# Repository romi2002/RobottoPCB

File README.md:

## Robotto PCB
PCB board designed to control a small, four wheeled robot, using a Teensy 4.0 as the main controller.

## Features
- Uses a `Teensy 4.0` or a `Teensy 4.1` (without soldering in the extra headers)
- 4 VNH5019A drivers
- Support for 5V or 3.3V encoders
- Raspberry PI GPIO compatible header
- Current and voltage monitoring
- Support for adding an IMU

## Warning!
This board has several known issues, further revisions to the PCB design have to be made.

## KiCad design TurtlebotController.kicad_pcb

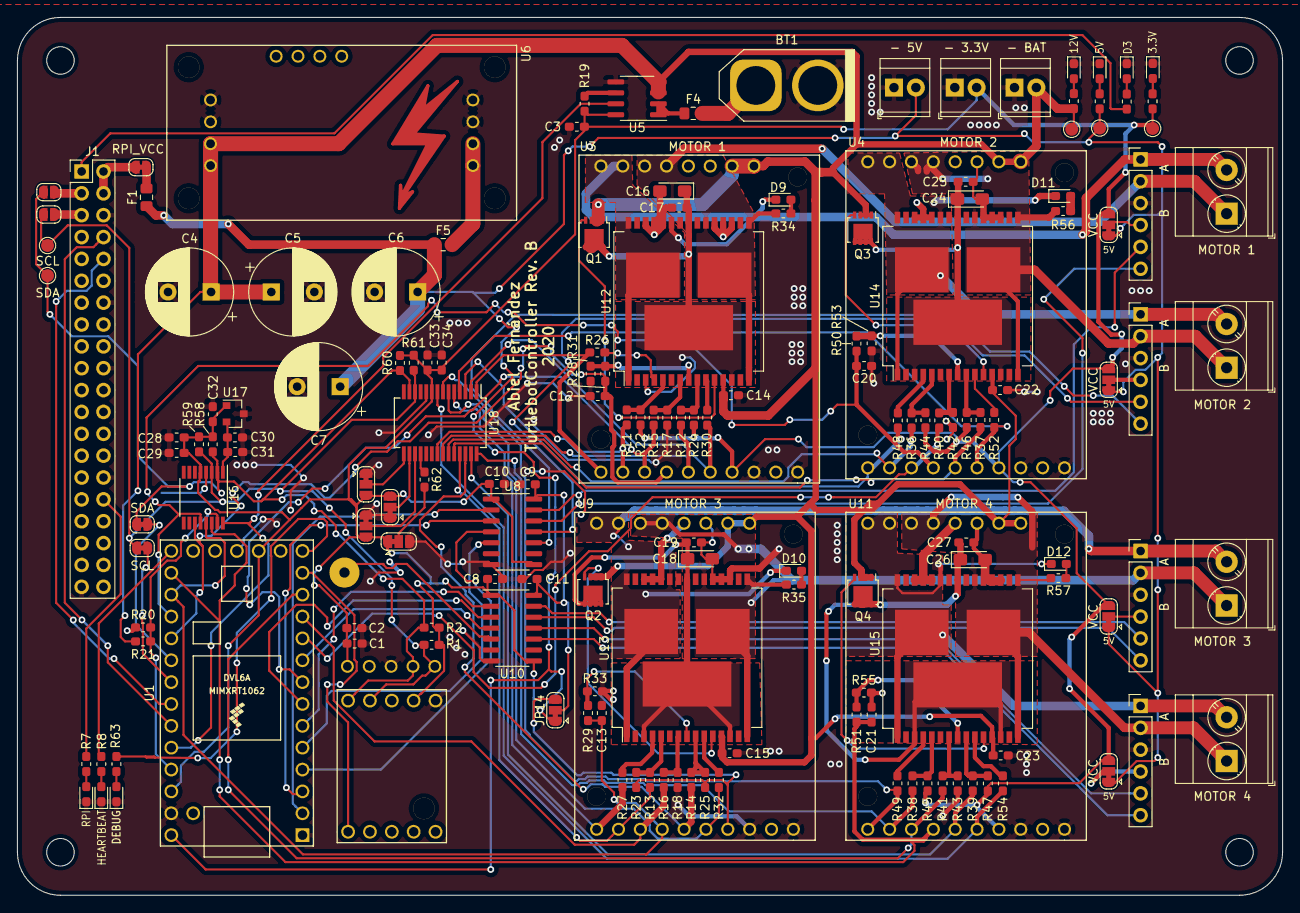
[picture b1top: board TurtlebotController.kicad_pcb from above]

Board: 2 copper layers, 147.0 x 102.0 mm, 164 parts (0 on the bottom side), 127 nets.

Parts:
3.3V: 3.3V_OK; LED_0603_1608Metric_Pad1.05x0.95mm_HandSolder
3.3V#2: 3.3V _OUT; TerminalBlock_TE_282834-2_1x02_P2.54mm_Horizontal
5V: 5V_OK; LED_0603_1608Metric_Pad1.05x0.95mm_HandSolder
5V#2: 5V_OUT; TerminalBlock_TE_282834-2_1x02_P2.54mm_Horizontal
12V: 12V_OK; LED_0603_1608Metric_Pad1.05x0.95mm_HandSolder
BAT: 12V_OUT; TerminalBlock_TE_282834-2_1x02_P2.54mm_Horizontal
BT1: Battery; AMASS_XT60-F_1x02_P7.20mm_Vertical
C1, C3, C8, C9, C10, C11, C14, C15, C17, C19, C22, C23, C25, C27, C29, C30, C34: 0.1uF; C_0603_1608Metric_Pad1.05x0.95mm_HandSolder
C2: 10uF; C_0603_1608Metric_Pad1.05x0.95mm_HandSolder
C4, C5, C6, C7: 1000uF; CP_Radial_D10.0mm_P5.00mm
C12, C13, C20, C21: 33nF; C_0603_1608Metric_Pad1.05x0.95mm_HandSolder
C16, C18, C24, C26: 47uF; CP_EIA-3216-10_Kemet-I_Pad1.58x1.35mm_HandSolder
C28, C31, C33: 1uF; C_0603_1608Metric_Pad1.05x0.95mm_HandSolder
C32: 0.47uF; C_0603_1608Metric_Pad1.05x0.95mm_HandSolder
D3: RASPI_3.3V_OK; LED_0603_1608Metric_Pad1.05x0.95mm_HandSolder
D9, D10, D11, D12: LED_Dual_2pin; LED_0603_1608Metric_Pad1.05x0.95mm_HandSolder
DEBUG: TEENSY_DEBUG; LED_0603_1608Metric_Pad1.05x0.95mm_HandSolder
F1, F4, F5: Fuse; Fuse_0805_2012Metric_Pad1.15x1.40mm_HandSolder
HEARTBEAT: TEENSY_HEARTBEAT; LED_0603_1608Metric_Pad1.05x0.95mm_HandSolder
J1: Raspberry_Pi_2_3; PinHeader_2x20_P2.54mm_Vertical
J2: MOTOR_1; PinHeader_1x06_P2.54mm_Vertical
J3: MOTOR_2; PinHeader_1x06_P2.54mm_Vertical
J7: MOTOR_3; PinHeader_1x06_P2.54mm_Vertical
J8: MOTOR_4; PinHeader_1x06_P2.54mm_Vertical
J9, J10, J11, J12: Screw_Terminal_01x02; TerminalBlock_Phoenix_MKDS-3-2-5.08_1x02_P5.08mm_Horizontal
JP4: RPI_SDA; SolderJumper-2_P1.3mm_Open_RoundedPad1.0x1.5mm
JP5: RPI_SCL; SolderJumper-2_P1.3mm_Open_RoundedPad1.0x1.5mm
JP10, JP11, JP12, JP13, JP14: Jumper_3_Bridged12; SolderJumper-3_P1.3mm_Bridged12_RoundedPad1.0x1.5mm
Q1, Q2, Q3, Q4: BUK7M12-40EX; LFPAK33
R1, R2, R22, R23, R24, R25, R34, R35, R44, R45, R46, R47, R56, R57, R58, R59, R60, R61, R62: 4.7k; R_0603_1608Metric_Pad1.05x0.95mm_HandSolder
R3: 560Ohm; R_0603_1608Metric_Pad1.05x0.95mm_HandSolder
R4: 150Ohm; R_0603_1608Metric_Pad1.05x0.95mm_HandSolder
R5, R6, R7, R8, R63: 65Ohm; R_0603_1608Metric_Pad1.05x0.95mm_HandSolder
R11, R12, R13, R14, R15, R16, R26, R27, R30, R31, R32, R33, R36, R37, R38, R39, R40, R41, R48, R49, R52, R53, R54, R55: 1k; R_0603_1608Metric_Pad1.05x0.95mm_HandSolder
R17, R18, R28, R29, R42, R43, R50, R51: 10k; R_0603_1608Metric_Pad1.05x0.95mm_HandSolder
R19: 10K; R_0603_1608Metric_Pad1.05x0.95mm_HandSolder
R20: 270 Ohm; R_0603_1608Metric_Pad1.05x0.95mm_HandSolder
R21: 70 Ohm; R_0603_1608Metric_Pad1.05x0.95mm_HandSolder
RPI: RASP_HEARTBEAT; LED_0603_1608Metric_Pad1.05x0.95mm_HandSolder
RPI_VCC: Jumper_NC_Small; SolderJumper-2_P1.3mm_Bridged_RoundedPad1.0x1.5mm
SCL: SCL_0; TestPoint_Pad_D1.5mm
SCL#2: SCL_TEENSY; SolderJumper-2_P1.3mm_Bridged_RoundedPad1.0x1.5mm
SDA: SDA_TEENSY; SolderJumper-2_P1.3mm_Bridged_RoundedPad1.0x1.5mm
SDA#2: SDA_0; TestPoint_Pad_D1.5mm
TP4: 3.3V; TestPoint_Pad_D1.5mm
TP5: 5V; TestPoint_Pad_D1.5mm
TP6: 12V; TestPoint_Pad_D1.5mm
TP17: TestPoint; SolderWirePad_1x01_Drill1.2mm
U1: Teensy4.0; Teensy40
U2: MinIMU-9_V5; Pololu_MinIMU-9
U3, U4, U9, U11: VNH5019; Pololu_VNH5019_Carrier
U5: ACS711xLCTR-25AB; SOIC-8_3.9x4.9mm_P1.27mm
U6: D24V90F5; Pololu_D24V90F5
U7: UltimateSensorFusion_MPU9250_PeskyProducts; UltimateSensorFusion_MPU9250
U8, U10: TXB0104D; SOIC-14_3.9x8.7mm_P1.27mm
U12, U13, U14, U15: VNH5019A-E; ST_MultiPowerSO-30
U16: ADC128D818; TSSOP-16_4.4x5mm_P0.65mm
U17: REF3030; SOT-23
U18: MCP23017_SS; SSOP-28_5.3x10.2mm_P0.65mm
VCC: Jumper_3_Bridged12; SolderJumper-3_P1.3mm_Bridged12_RoundedPad1.0x1.5mm
VCC#2, VCC#3, VCC#4: Jumper_3_Bridged12; SolderJumper-3_P1.3mm_Bridged12_RoundedPad1.0x1.5mm

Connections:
+3V3: 3.3V#2.2, C1.1, C2.1, C3.2, C8.1, C10.1, C28.1, C29.2, C32.1, C33.1, C34.2, JP10.3, JP11.1, JP12.3, JP13.3, JP14.3, R1.1, R2.2, R6.2, R19.1, R22.2, R23.2, R24.2, R25.2, R44.2, R45.2, R46.2, R47.2, R58.2, R59.1, R60.1, R61.2, TP4.1, U1.16, U1.31, U2.5, U3.7, U4.7, U5.8, U7.2, U8.1, U8.8, U9.7, U10.1, U10.8, U11.7, U16.5, U17.1, U18.9, VCC.3, VCC#2.3, VCC#3.3, VCC#4.3
+5V: 5V#2.2, C6.1, C7.1, F1.1, F5.1, JP14.1, R4.2, TP5.1, U1.33, VCC.1, VCC#2.1, VCC#3.1, VCC#4.1
+12V: BAT.2, C4.1, C5.1, C14.1, C15.1, C22.1, C23.1, Q1.1, Q1.2, Q1.3, Q2.1, Q2.2, Q2.3, Q3.1, Q3.2, Q3.3, Q4.1, Q4.2, Q4.3, R3.2, R20.1, TP6.1, U3.14, U4.14, U5.3, U5.4, U6.4, U9.14, U11.14, U12.12, U13.12, U14.12, U15.12
ADC_VREF: C30.1, C31.1, U16.1, U17.2
BAT_VOLTAGE: R20.2, R21.1, U1.30, U16.15
CURRENT_FAULT: R19.2, U5.6
CURRENT_OUT: U1.29, U5.7, U16.16
GND: 3.3V.1, 3.3V#2.1, 5V.1, 5V#2.1, 12V.1, BAT.1, BT1.2, C1.2, C2.2, C3.1, C4.2, C5.2, C6.2, C7.2, C8.2, C9.1, C10.2, C11.1, C12.1, C13.1, C14.2, C15.2, C16.2, C17.1, C18.2, C19.1, C20.1, C21.1, C22.2, C23.2, C24.2, C25.1, C26.2, C27.1, C28.2, C29.1, C30.2, C31.2, C32.2, C33.2, C34.1, D3.1, DEBUG.1, HEARTBEAT.1, J1.6, J1.9, J1.14, J1.20, J1.25, J1.30, J1.34, J1.39, J2.3, J3.3, J7.3, J8.3, JP10.1, JP11.3, JP12.1, JP13.1, R17.2, R18.2, R21.2, R31.1, R33.1, R42.2, R43.2, R53.1, R55.1, RPI.1, U1.1, U1.17, U1.32, U2.3, U3.8, U3.10, U3.13, U4.8, U4.10, U4.13, U5.5, U6.1, U6.3, U7.1, U8.7, U9.8, U9.10, U9.13, U10.7, U11.8, U11.10, U11.13, U12.18, U12.19, U12.20, U12.26, U12.27, U12.28, U13.18, U13.19, U13.20, U13.26, U13.27, U13.28, U14.18, U14.19, U14.20, U14.26, U14.27, U14.28, U15.18, U15.19, U15.20, U15.26, U15.27, U15.28, U16.4, U17.3, U18.10
MOTOR_1_A: D9.1, J2.1, J9.2, U3.11, U12.1, U12.25, U12.30, U12.33
MOTOR_1_B: J2.2, J9.1, R34.1, U3.12, U12.15, U12.16, U12.21, U12.32
MOTOR_1_CS: C12.2, R28.1, U1.24, U3.4, U16.11
MOTOR_1_DIAGA: R11.1, U3.2, U18.21
MOTOR_1_DIAGB: R12.1, U3.5, U18.22
MOTOR_1_ENCODER_A: U1.2, U8.2
MOTOR_1_ENCODER_A_5V: J2.5, U8.13
MOTOR_1_ENCODER_B: U1.3, U8.3
MOTOR_1_ENCODER_B_5V: J2.6, U8.12
MOTOR_1_INA: R26.1, U3.1, U18.1
MOTOR_1_INB: R30.1, U3.6, U18.2
MOTOR_1_PWM: R15.1, U1.8, U3.3
MOTOR_2_A: D11.1, J3.1, J10.2, U4.11, U14.1, U14.25, U14.30, U14.33
MOTOR_2_B: J3.2, J10.1, R56.1, U4.12, U14.15, U14.16, U14.21, U14.32
MOTOR_2_CS: C20.2, R50.1, U1.23, U4.4, U16.12
MOTOR_2_DIAGA: R36.1, U4.2, U18.23
MOTOR_2_DIAGB: R37.1, U4.5, U18.24
MOTOR_2_ENCODER_A: U1.4, U8.4
MOTOR_2_ENCODER_A_5V: J3.5, U8.11
MOTOR_2_ENCODER_B: U1.5, U8.5
MOTOR_2_ENCODER_B_5V: J3.6, U8.10
MOTOR_2_INA: R48.1, U4.1, U18.3
MOTOR_2_INB: R52.1, U4.6, U18.4
MOTOR_2_PWM: R40.1, U1.10, U4.3
MOTOR_3_A: D10.1, J7.1, J11.2, U9.11, U13.1, U13.25, U13.30, U13.33
MOTOR_3_B: J7.2, J11.1, R35.1, U9.12, U13.15, U13.16, U13.21, U13.32
MOTOR_3_CS: C13.2, R29.1, U1.22, U9.4, U16.13
MOTOR_3_DIAGA: R13.1, U9.2, U18.25
MOTOR_3_DIAGB: R14.1, U9.5, U18.26
MOTOR_3_ENCODER_A: U1.6, U10.2
MOTOR_3_ENCODER_A_5V: J7.5, U10.13
MOTOR_3_ENCODER_B: U1.7, U10.3
MOTOR_3_ENCODER_B_5V: J7.6, U10.12
MOTOR_3_INA: R27.1, U9.1, U18.5
MOTOR_3_INB: R32.1, U9.6, U18.6
MOTOR_3_PWM: R16.1, U1.11, U9.3
MOTOR_4_A: D12.1, J8.1, J12.2, U11.11, U15.1, U15.25, U15.30, U15.33
MOTOR_4_B: J8.2, J12.1, R57.1, U11.12, U15.15, U15.16, U15.21, U15.32
MOTOR_4_CS: C21.2, R51.1, U1.21, U11.4, U16.14
MOTOR_4_DIAGA: R38.1, U11.2, U18.28
MOTOR_4_DIAGB: R39.1, U11.5, U18.27
MOTOR_4_ENCODER_A: U1.9, U10.4
MOTOR_4_ENCODER_A_5V: J8.5, U10.11
MOTOR_4_ENCODER_B: TP17.1, U10.5
MOTOR_4_ENCODER_B_5V: J8.6, U10.10
MOTOR_4_INA: R49.1, U11.1, U18.7
MOTOR_4_INB: R54.1, U11.6, U18.8
MOTOR_4_PWM: R41.1, U1.12, U11.3
MPU_INTERRUPT: U1.13, U7.10
unnamed: BT1.1, F4.2
unnamed: C9.2, C11.2, JP14.2, U8.14, U10.14
unnamed: C16.1, C17.2, Q1.5, U12.3, U12.13, U12.23, U12.31
unnamed: C18.1, C19.2, Q2.5, U13.3, U13.13, U13.23, U13.31
unnamed: C24.1, C25.2, Q3.5, U14.3, U14.13, U14.23, U14.31
unnamed: C26.1, C27.2, Q4.5, U15.3, U15.13, U15.23, U15.31
unnamed: 12V.2, R3.1
unnamed: 5V.2, R4.1
unnamed: D3.2, R5.1
unnamed: 3.3V.2, R6.1
unnamed: R7.1, RPI.2
unnamed: HEARTBEAT.2, R8.1
unnamed: D9.2, R34.2
unnamed: D10.2, R35.2
unnamed: D11.2, R56.2
unnamed: D12.2, R57.2
unnamed: DEBUG.2, R63.1
unnamed: F1.2, RPI_VCC.2
unnamed: F4.1, U5.1, U5.2
unnamed: F5.2, U6.2
unnamed: J1.2, J1.4, RPI_VCC.1
unnamed: J1.3, JP4.1
unnamed: J1.5, JP5.1
unnamed: J2.4, VCC.2
unnamed: J3.4, VCC#3.2
unnamed: J7.4, VCC#2.2
unnamed: J8.4, VCC#4.2
unnamed: SDA.2, U1.25
unnamed: SCL#2.2, U1.26
unnamed: JP10.2, U18.16
unnamed: JP11.2, R62.2
unnamed: JP12.2, U18.17
unnamed: JP13.2, U18.15
unnamed: Q1.4, U12.11
unnamed: Q2.4, U13.11
unnamed: Q3.4, U14.11
unnamed: Q4.4, U15.11
unnamed: R11.2, R22.1, U12.5
unnamed: R12.2, R24.1, U12.9
unnamed: R13.2, R23.1, U13.5
unnamed: R14.2, R25.1, U13.9
unnamed: R15.2, R17.1, U12.7
unnamed: R16.2, R18.1, U13.7
unnamed: R26.2, U12.4
unnamed: R27.2, U13.4
unnamed: R28.2, R31.2, U12.8
unnamed: R29.2, R33.2, U13.8
unnamed: R30.2, U12.10
unnamed: R32.2, U13.10
unnamed: R36.2, R44.1, U14.5
unnamed: R37.2, R46.1, U14.9
unnamed: R38.2, R45.1, U15.5
unnamed: R39.2, R47.1, U15.9
unnamed: R40.2, R42.1, U14.7
unnamed: R41.2, R43.1, U15.7
unnamed: R48.2, U14.4
unnamed: R49.2, U15.4
unnamed: R50.2, R53.2, U14.8
unnamed: R51.2, R55.2, U15.8
unnamed: R52.2, U14.10
unnamed: R54.2, U15.10
unnamed: R62.1, U18.18
RASPBERRY_3.3V: J1.1, J1.17, R5.2
RASPBERRY_HEARTBEAT: J1.32, R7.2
SCL_0: JP5.2, R1.2, R59.2, R61.1, SCL.1, SCL#2.1, U2.1, U7.4, U16.3, U18.12
SDA_0: JP4.2, R2.1, R58.1, R60.2, SDA.1, SDA#2.1, U2.2, U7.5, U16.2, U18.13
TEENSY_DEBUG: R63.2, U1.14
TEENSY_HEARTBEAT: R8.2, U1.20
TEENSY_RX: J1.8, U1.28
TEENSY_TX: J1.10, U1.27

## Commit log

2019-12-01 Added fuses
2019-12-02 Added footprints
2020-04-20 Added BOM
2020-05-16 Some fixes
2020-05-16 Most of rev B
2020-05-17 RevB
2020-06-04 Rev B
2021-01-14 Add media
2021-01-14 Added readme (#1)
    * Add media
    * Create README.md
2021-01-14 Reorganized
